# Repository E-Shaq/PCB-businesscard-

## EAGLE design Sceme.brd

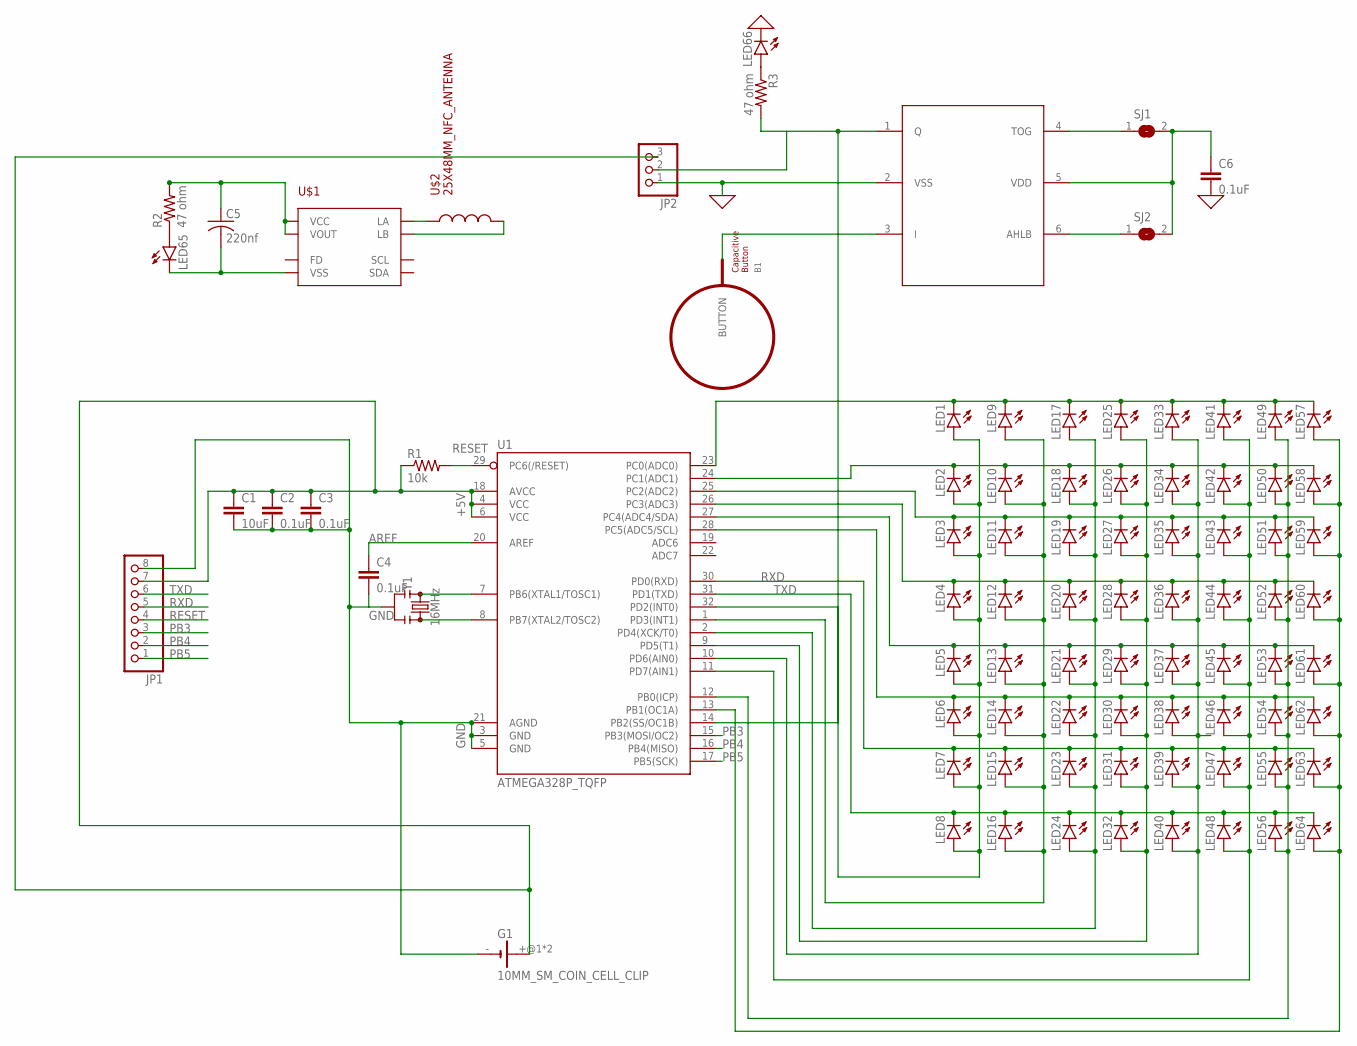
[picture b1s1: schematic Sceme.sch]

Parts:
B1: BUTTON_PASSIVE8MM; BUTTON_PASSIVE_8MM
C1: 10uF; C0603
C2, C3, C4, C6: 0.1uF; C0603
C5: 220nf; C0805
G1: 10MM_SM_COIN_CELL_CLIP
JP1: PINHD-1X8; 1X08
JP2: PINHD-1X3; 1X03
LED1, LED2, LED3, LED4, LED5, LED6, LED7, LED8, LED9, LED10, LED11, LED12, LED13, LED14, LED15, LED16, LED17, LED18, LED19, LED20, LED21, LED22, LED23, LED24, LED25, LED26, LED27, LED28, LED29, LED30, LED31, LED32, LED33, LED34, LED35, LED36, LED37, LED38, LED39, LED40, LED41, LED42, LED43, LED44, LED45, LED46, LED47, LED48, LED49, LED50, LED51, LED52, LED53, LED54, LED55, LED56, LED57, LED58, LED59, LED60, LED61, LED62, LED63, LED64: LED; SMARTLED-TTW
LED65, LED66: LEDSML0805; SML0805
R1: 10k; R0603
R2, R3: 47 ohm; R0805
SJ1, SJ2: SJ
U1: ATMEGA328P_TQFP; TQFP32-08
U$1: NT3H; XQFN8
U$2: 25X48MM_NFC_ANTENNA
U$9: TTP223; SOT23-6
Y1: 16MHz; RESONATOR-SMD-3.2X1.3

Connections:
0: C6.2, JP2.1, LED66.C, U$9.2 (VSS)
+5V: C1.1, C2.1, C3.1, G1.+@1 (+), G1.+@2 (+), JP1.7, JP2.3, R1.1, U1.4 (VCC), U1.6 (VCC), U1.18 (AVCC)
AREF: C4.1, U1.20 (AREF)
GND: C1.2, C2.2, C3.2, C4.2, G1.-, JP1.8, U1.3 (GND), U1.5 (GND), U1.21 (AGND), Y1.2
unnamed: LED1.C@1 (C), LED9.C@1 (C), LED17.C@1 (C), LED25.C@1 (C), LED33.C@1 (C), LED41.C@1 (C), LED49.C@1 (C), LED57.C@1 (C), U1.23 (PC0(ADC0))
unnamed: LED2.C@1 (C), LED10.C@1 (C), LED18.C@1 (C), LED26.C@1 (C), LED34.C@1 (C), LED42.C@1 (C), LED50.C@1 (C), LED58.C@1 (C), U1.24 (PC1(ADC1))
unnamed: LED3.C@1 (C), LED11.C@1 (C), LED19.C@1 (C), LED27.C@1 (C), LED35.C@1 (C), LED43.C@1 (C), LED51.C@1 (C), LED59.C@1 (C), U1.25 (PC2(ADC2))
unnamed: LED4.C@1 (C), LED12.C@1 (C), LED20.C@1 (C), LED28.C@1 (C), LED36.C@1 (C), LED44.C@1 (C), LED52.C@1 (C), LED60.C@1 (C), U1.26 (PC3(ADC3))
unnamed: LED5.C@1 (C), LED13.C@1 (C), LED21.C@1 (C), LED29.C@1 (C), LED37.C@1 (C), LED45.C@1 (C), LED53.C@1 (C), LED61.C@1 (C), U1.27 (PC4(ADC4/SDA))
unnamed: LED6.C@1 (C), LED14.C@1 (C), LED22.C@1 (C), LED30.C@1 (C), LED38.C@1 (C), LED46.C@1 (C), LED54.C@1 (C), LED62.C@1 (C), U1.28 (PC5(ADC5/SCL))
unnamed: U$1.LA, U$2.P$1
unnamed: U$1.LB, U$2.P$2
unnamed: LED1.A@1 (A), LED2.A@1 (A), LED3.A@1 (A), LED4.A@1 (A), LED5.A@1 (A), LED6.A@1 (A), LED7.A@1 (A), LED8.A@1 (A), U1.32 (PD2(INT0))
unnamed: LED9.A@1 (A), LED10.A@1 (A), LED11.A@1 (A), LED12.A@1 (A), LED13.A@1 (A), LED14.A@1 (A), LED15.A@1 (A), LED16.A@1 (A), U1.1 (PD3(INT1))
unnamed: LED17.A@1 (A), LED18.A@1 (A), LED19.A@1 (A), LED20.A@1 (A), LED21.A@1 (A), LED22.A@1 (A), LED23.A@1 (A), LED24.A@1 (A), U1.2 (PD4(XCK/T0))
unnamed: LED25.A@1 (A), LED26.A@1 (A), LED27.A@1 (A), LED28.A@1 (A), LED29.A@1 (A), LED30.A@1 (A), LED31.A@1 (A), LED32.A@1 (A), U1.9 (PD5(T1))
unnamed: LED33.A@1 (A), LED34.A@1 (A), LED35.A@1 (A), LED36.A@1 (A), LED37.A@1 (A), LED38.A@1 (A), LED39.A@1 (A), LED40.A@1 (A), U1.10 (PD6(AIN0))
unnamed: LED41.A@1 (A), LED42.A@1 (A), LED43.A@1 (A), LED44.A@1 (A), LED45.A@1 (A), LED46.A@1 (A), LED47.A@1 (A), LED48.A@1 (A), U1.11 (PD7(AIN1))
unnamed: LED49.A@1 (A), LED50.A@1 (A), LED51.A@1 (A), LED52.A@1 (A), LED53.A@1 (A), LED54.A@1 (A), LED55.A@1 (A), LED56.A@1 (A), U1.12 (PB0(ICP))
unnamed: LED57.A@1 (A), LED58.A@1 (A), LED59.A@1 (A), LED60.A@1 (A), LED61.A@1 (A), LED62.A@1 (A), LED63.A@1 (A), LED64.A@1 (A), U1.13 (PB1(OC1A))
unnamed: U1.7 (PB6(XTAL1/TOSC1)), Y1.1
unnamed: U1.8 (PB7(XTAL2/TOSC2)), Y1.3
unnamed: LED65.A, R2.1
unnamed: C5.1, R2.2, U$1.VCC, U$1.VOUT
unnamed: C5.2, LED65.C, U$1.VSS
unnamed: LED66.A, R3.1
unnamed: JP2.2, R3.2, U1.14 (PB2(SS/OC1B)), U$9.1 (Q)
unnamed: B1.BUTTON, U$9.3 (I)
unnamed: SJ1.1, U$9.4 (TOG)
unnamed: SJ2.1, U$9.6 (AHLB)
unnamed: C6.1, SJ1.2, SJ2.2, U$9.5 (VDD)
PB3: JP1.3, U1.15 (PB3(MOSI/OC2))
PB4: JP1.2, U1.16 (PB4(MISO))
PB5: JP1.1, U1.17 (PB5(SCK))
RESET: JP1.4, R1.2, U1.29 (PC6(/RESET))
RXD: JP1.5, LED7.C@1 (C), LED15.C@1 (C), LED23.C@1 (C), LED31.C@1 (C), LED39.C@1 (C), LED47.C@1 (C), LED55.C@1 (C), LED63.C@1 (C), U1.30 (PD0(RXD))
TXD: JP1.6, LED8.C@1 (C), LED16.C@1 (C), LED24.C@1 (C), LED32.C@1 (C), LED40.C@1 (C), LED48.C@1 (C), LED56.C@1 (C), LED64.C@1 (C), U1.31 (PD1(TXD))

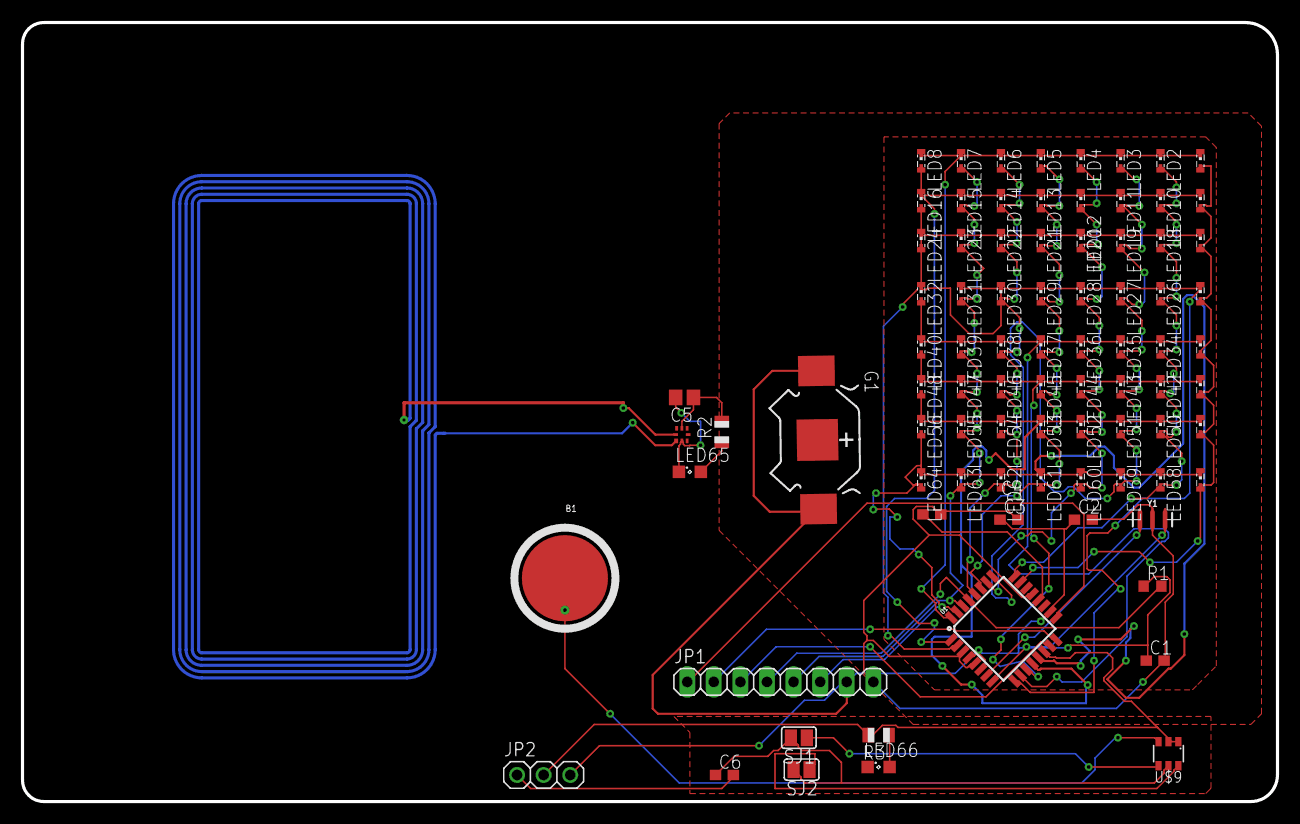
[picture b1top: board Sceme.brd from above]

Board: 2 copper layers, 119.9 x 74.4 mm, 86 parts (1 on the bottom side), 37 nets.

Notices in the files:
parts and their libraries:
PatternAgents-TouchWidgets: License : http://creativecommons.org/licenses/by-sa/4.0/ (Creative Commons 4.0)
PatternAgents-TouchWidgets: License : http://creativecommons.org/licenses/by-sa/3.1/ (Creative Commons 3.1)
